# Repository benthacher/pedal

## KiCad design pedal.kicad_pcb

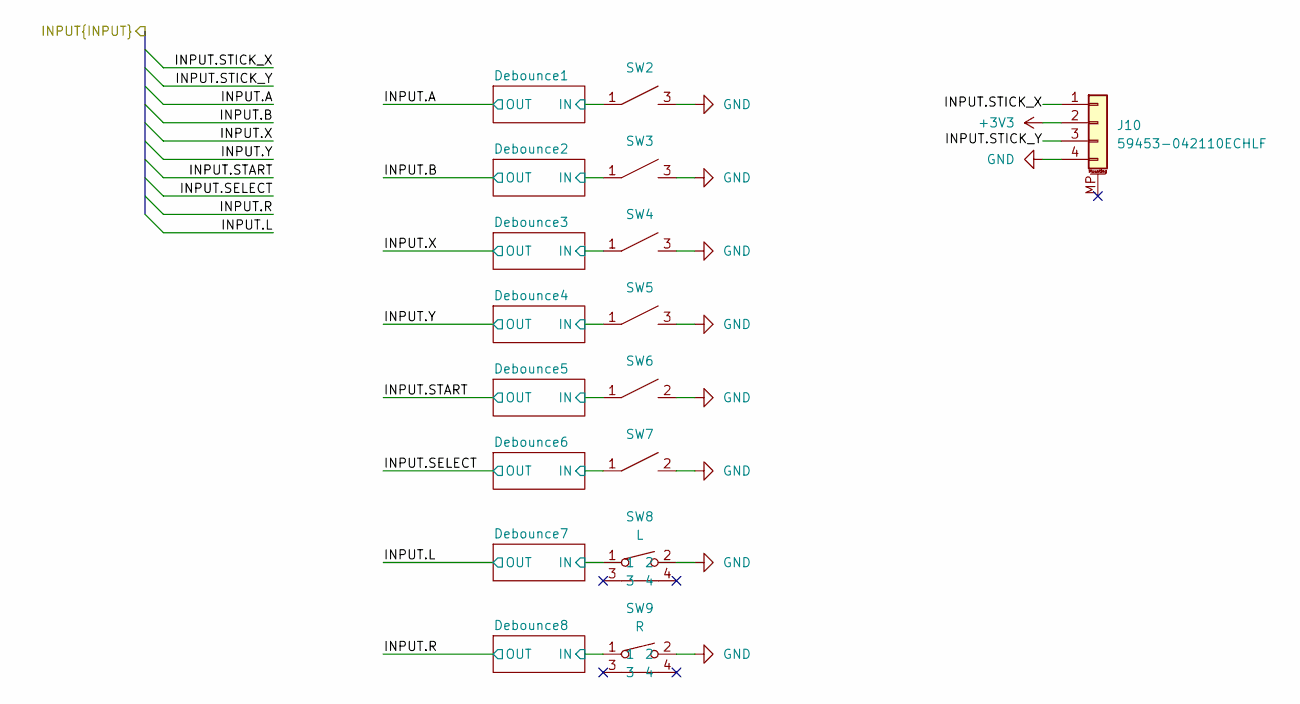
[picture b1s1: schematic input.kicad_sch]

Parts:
J10: 59453-042110ECHLF; AMPHENOL_59453-042110ECHLF; LCSC C3169529
SW2: A; SW-SMD_4P-L4.5-W4.5-P3.50-LS4.8; MPN TL3315NF100Q; LCSC Part C173769
SW3: B; SW-SMD_4P-L4.5-W4.5-P3.50-LS4.8; MPN TL3315NF100Q; LCSC Part C173769
SW4: X; SW-SMD_4P-L4.5-W4.5-P3.50-LS4.8; MPN TL3315NF100Q; LCSC Part C173769
SW5: Y; SW-SMD_4P-L4.5-W4.5-P3.50-LS4.8; MPN TL3315NF100Q; LCSC Part C173769
SW6: START; SW-SMD_L3.9-W3.0-P4.45; MPN TS-1088-AR02016; LCSC Part C720477
SW7: SELECT; SW-SMD_L3.9-W3.0-P4.45; MPN TS-1088-AR02016; LCSC Part C720477
SW8: L; SW-SMD_L4.7-W3.5-P3.35-EH; MPN TS-24CA-S26; LCSC Part C42420265
SW9: R; SW-SMD_L4.7-W3.5-P3.35-EH; MPN TS-24CA-S26; LCSC Part C42420265

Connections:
+3V3: J10.2; also elsewhere on the board
/Input/Debounce1/IN: SW2.1, SW2.2; also elsewhere on the board
/Input/Debounce2/IN: SW3.1, SW3.2; also elsewhere on the board
/Input/Debounce3/IN: SW4.1, SW4.2; also elsewhere on the board
/Input/Debounce4/IN: SW5.1, SW5.2; also elsewhere on the board
/Input/Debounce5/IN: SW6.1; also elsewhere on the board
/Input/Debounce6/IN: SW7.1; also elsewhere on the board
/Input/Debounce7/IN: SW8.1; also elsewhere on the board
/Input/Debounce8/IN: SW9.1; also elsewhere on the board
/Input/INPUT.STICK_X: J10.1; also elsewhere on the board
/Input/INPUT.STICK_Y: J10.3; also elsewhere on the board
GND: J10.4, SW2.3, SW2.4, SW3.3, SW3.4, SW4.3, SW4.4, SW5.3, SW5.4, SW6.2, SW7.2, SW8.2, SW9.2; also elsewhere on the board

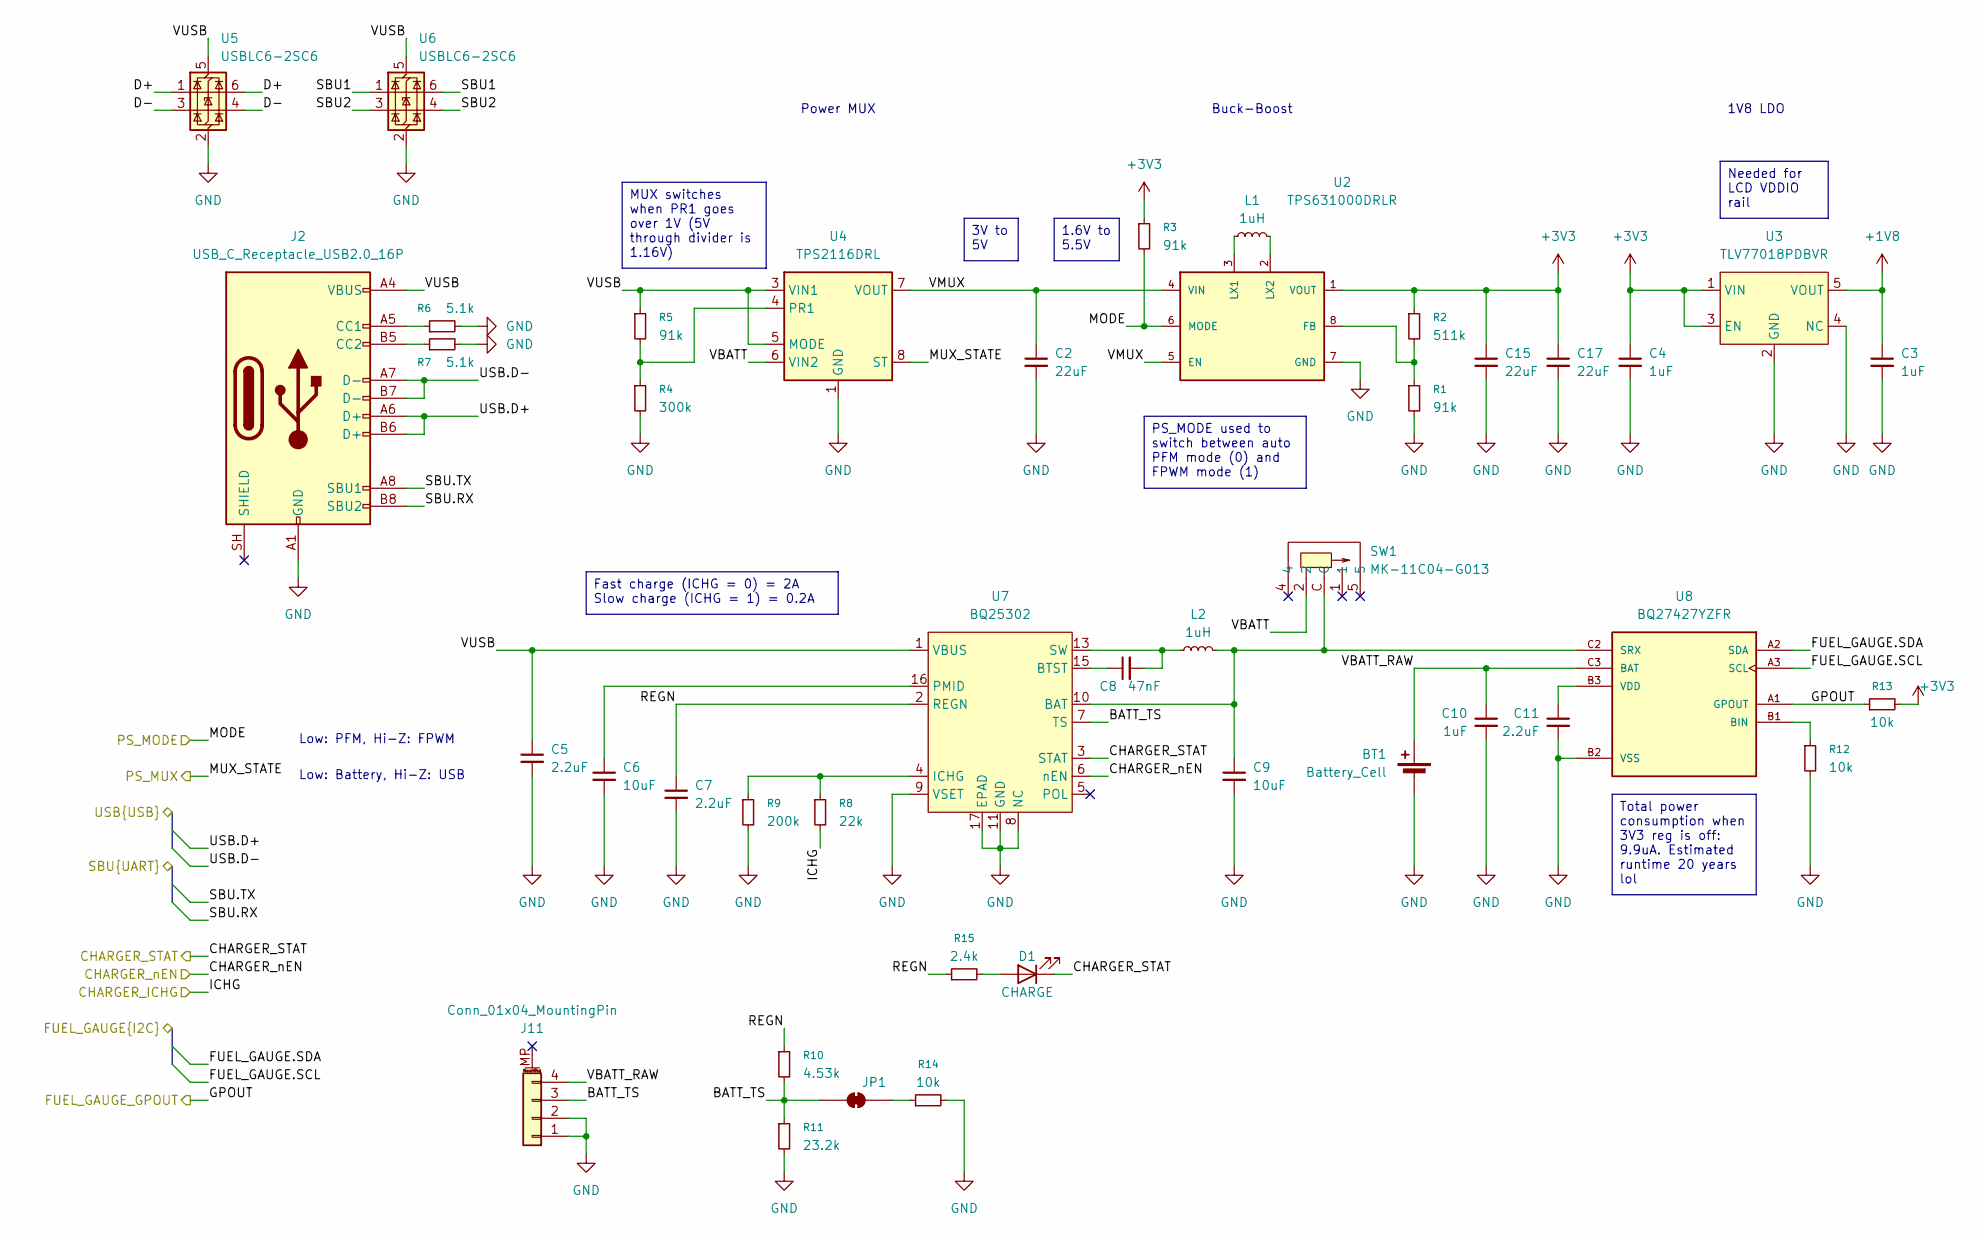
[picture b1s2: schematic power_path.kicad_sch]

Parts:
BT1: Battery_Cell
C2, C15, C17: 22uF; C_0805_2012Metric; Voltage 25V; LCSC C45783
C3: 1uF; C_0402_1005Metric; LCSC C52923
C4, C10: 1uF; C_0402_1005Metric; voltage 25; LCSC C52923
C5, C7, C11: 2.2uF; C_0603_1608Metric; Voltage 16; LCSC C23630
C6, C9: 10uF; C_0603_1608Metric; Voltage 25; LCSC C96446
C8: 47nF; C_0603_1608Metric; Voltage 50; LCSC C1622
D1: CHARGE; LED_0402_1005Metric; LCSC C5123495
J2: USB_C_Receptacle_USB2.0_16P; USB_C_Receptacle_HRO_TYPE-C-31-M-12; LCSC C165948
J11: Conn_01x04_MountingPin; CONN-SMD_4P-P1.00_2121340004
JP1: SolderJumper-2_P1.3mm_Bridged2Bar_RoundedPad1.0x1.5mm
L1, L2: 1uH; L_1008_2520Metric; LCSC C882955
R1, R3, R5: 91k; R_0402_1005Metric; LCSC C327323
R2: 511k; R_0402_1005Metric; LCSC C64042
R4: 300k; R_0402_1005Metric; LCSC C25774
R6, R7: 5.1k; R_0402_1005Metric; LCSC C25905
R8: 22k; R_0402_1005Metric; LCSC C25768
R9: 200k; R_0402_1005Metric; LCSC C25764
R10: 4.53k; R_0402_1005Metric; LCSC C79537
R11: 23.2k; R_0402_1005Metric; LCSC C25873
R12, R13, R14: 10k; R_0402_1005Metric; LCSC C25744
R15: 2.4k; R_0402_1005Metric; LCSC C25882
SW1: MK-11C04-G013; SW-SMD_MK-11C04-G013; MPN MK-11C04-G013; LCSC Part C778185
U2: TPS631000DRLR; SOT50P160X60-8N; PARTREV B; DigiKey_Part_Number 296-TPS631000DRLRCT-ND
U3: TLV77018PDBVR; SOT-23-5
U4: TPS2116DRL; SOT-583-8
U5, U6: USBLC6-2SC6; SOT-23-6; LCSC C5180249
U7: BQ25302; WQFN-16-1EP_3x3mm_P0.5mm_EP1.68x1.68mm_ThermalVias; LCSC C2761617
U8: BQ27427YZFR; IC_BQ27427YZFR; PARTREV December 2022; DigiKey_Part_Number 296-BQ27427YZFRCT-ND

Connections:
+1V8: C3.1, U3.5 (VOUT); also elsewhere on the board
+3V3: C4.1, C15.1, C17.1, R2.1, R3.1, R13.2, U2.1 (VOUT), U3.1 (VIN), U3.3 (EN); also elsewhere on the board
/Power path/BATT_TS: J11.3, JP1.1 (A), R10.2, R11.1, U7.7 (TS)
/Power path/CHARGER_STAT: D1.1 (K), U7.3 (STAT); also elsewhere on the board
/Power path/CHARGER_nEN: U7.6 (nEN); also elsewhere on the board
/Power path/D+: U5.1 (I/O1), U5.6 (I/O1)
/Power path/D-: U5.3 (I/O2), U5.4 (I/O2)
/Power path/FUEL_GAUGE.SCL: U8.A3 (SCL); also elsewhere on the board
/Power path/FUEL_GAUGE.SDA: U8.A2 (SDA); also elsewhere on the board
/Power path/GPOUT: R13.1, U8.A1 (GPOUT); also elsewhere on the board
/Power path/ICHG: R8.2; also elsewhere on the board
/Power path/MODE: R3.2, U2.6 (MODE); also elsewhere on the board
/Power path/MUX_STATE: U4.8 (ST); also elsewhere on the board
/Power path/REGN: C7.1, R10.1, R15.1, U7.2 (REGN)
/Power path/SBU1: U6.1 (I/O1), U6.6 (I/O1)
/Power path/SBU2: U6.3 (I/O2), U6.4 (I/O2)
/Power path/SBU.RX: J2.B8 (SBU2); also elsewhere on the board
/Power path/SBU.TX: J2.A8 (SBU1); also elsewhere on the board
/Power path/USB.D+: J2.A6 (D+), J2.B6 (D+); also elsewhere on the board
/Power path/USB.D-: J2.A7 (D-), J2.B7 (D-); also elsewhere on the board
/Power path/VBATT: SW1.2, U4.6 (VIN2)
/Power path/VBATT_RAW: BT1.1 (+), C10.1, J11.4, U8.C3 (BAT)
/Power path/VMUX: C2.1, U2.4 (VIN), U2.5 (EN), U4.2 (VOUT), U4.7 (VOUT)
/Power path/VUSB: C5.1, J2.A4 (VBUS), J2.A9 (VBUS), J2.B4 (VBUS), J2.B9 (VBUS), R5.1, U4.3 (VIN1), U4.5 (MODE), U5.5 (VBUS), U6.5 (VBUS), U7.1 (VBUS)
GND: BT1.2 (-), C2.2, C3.2, C4.2, C5.2, C6.2, C7.2, C9.2, C10.2, C11.2, C15.2, C17.2, J2.A1 (GND), J2.A12 (GND), J2.B1 (GND), J2.B12 (GND), J11.1, J11.2, R1.2, R4.2, R6.2, R7.2, R9.2, R11.2, R12.2, R14.2, U2.7 (GND), U3.2 (GND), U3.4 (NC), U4.1 (GND), U5.2 (GND), U6.2 (GND), U7.8 (NC), U7.9 (VSET), U7.11 (GND), U7.12 (GND), U7.17 (EPAD), U8.B2 (VSS), U8.C1 (VSS); also elsewhere on the board
unnamed: C8.2, L2.1, U7.13 (SW), U7.14 (SW)
unnamed: D1.2 (A), R15.2
unnamed: J2.A5 (CC1), R6.1
unnamed: J2.B5 (CC2), R7.1
unnamed: JP1.2 (B), R14.1
unnamed: R1.1, R2.2, U2.8 (FB)
unnamed: L1.1, U2.3 (LX1)
unnamed: L1.2, U2.2 (LX2)
unnamed: R4.1, R5.2, U4.4 (PR1)
unnamed: C9.1, L2.2, SW1.C, U7.10 (BAT), U8.C2 (SRX)
unnamed: C8.1, U7.15 (BTST)
unnamed: R8.1, R9.1, U7.4 (ICHG)
unnamed: C6.1, U7.16 (PMID)
unnamed: R12.1, U8.B1 (BIN)
unnamed: C11.1, U8.B3 (VDD)

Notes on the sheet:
Low: Battery, Hi-Z: USB
1V8 LDO
Buck-Boost
Low: PFM, Hi-Z: FPWM
Power MUX
Total power consumption when 3V3 reg is off: 9.9uA. Estimated runtime 20 years lol
3V to 5V
Needed for LCD VDDIO rail
MUX switches when PR1 goes over 1V (5V through divider is 1.16V)
1.6V to 5.5V
Fast charge (ICHG = 0) = 2A Slow charge (ICHG = 1) = 0.2A
PS_MODE used to switch between auto PFM mode (0) and FPWM mode (1)

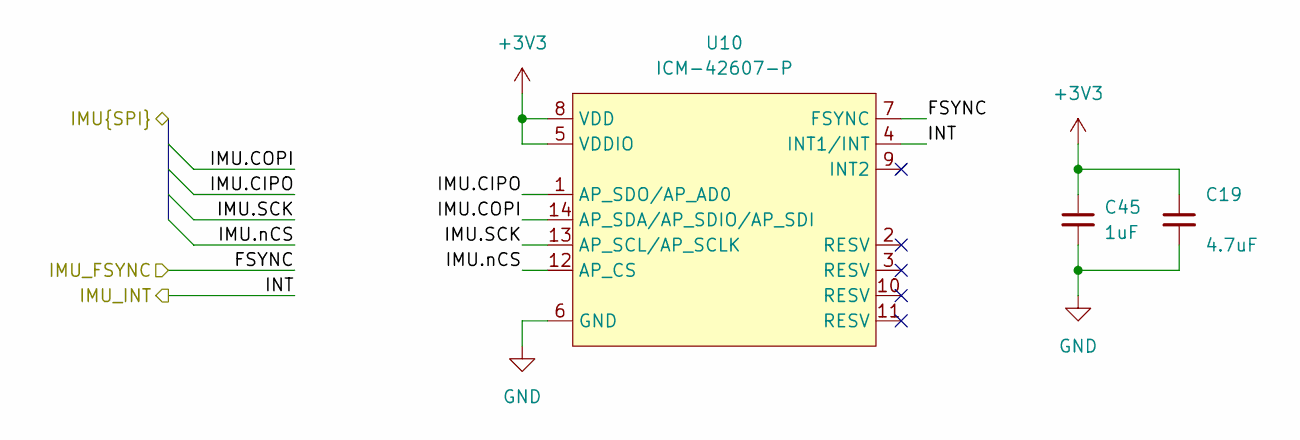
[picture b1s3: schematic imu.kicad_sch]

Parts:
C19: 4.7uF; C_0402_1005Metric; LCSC C23733
C45: 1uF; C_0402_1005Metric; voltage 25; LCSC C52923
U10: ICM-42607-P; LGA-14_L3.0-W2.5-P0.50-TL_QMI8658A; MPN ICM-42607-P; LCSC Part C5129967

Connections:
+3V3: C19.1, C45.1, U10.5 (VDDIO), U10.8 (VDD); also elsewhere on the board
/IMU/FSYNC: U10.7 (FSYNC); also elsewhere on the board
/IMU/IMU.CIPO: U10.1 (AP_SDO/AP_AD0); also elsewhere on the board
/IMU/IMU.COPI: U10.14 (AP_SDA/AP_SDIO/AP_SDI); also elsewhere on the board
/IMU/IMU.SCK: U10.13 (AP_SCL/AP_SCLK); also elsewhere on the board
/IMU/IMU.nCS: U10.12 (AP_CS); also elsewhere on the board
/IMU/INT: U10.4 (INT1/INT); also elsewhere on the board
GND: C19.2, C45.2, U10.6 (GND); also elsewhere on the board

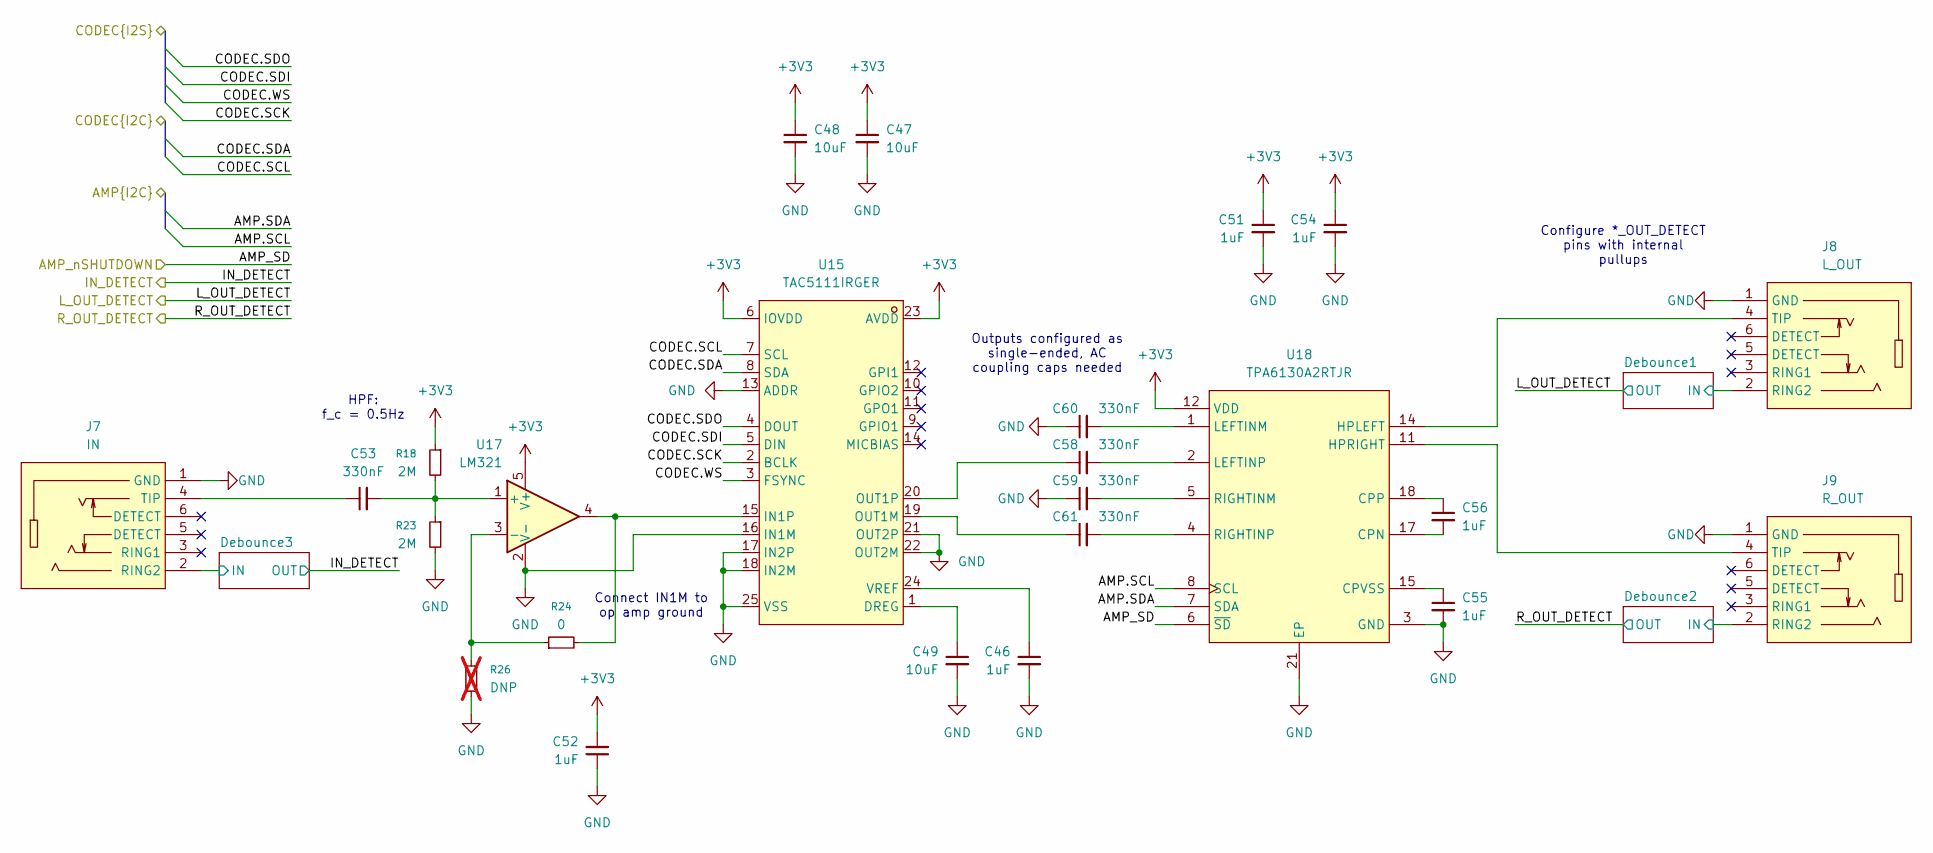
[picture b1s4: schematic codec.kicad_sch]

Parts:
C46, C51, C52, C54, C55, C56: 1uF; C_0402_1005Metric; voltage 25; LCSC C52923
C47, C48, C49: 10uF; C_0603_1608Metric; Voltage 25; LCSC C96446
C53, C58, C59, C60, C61: 330nF; C_1206_3216Metric; Voltage 25; LCSC C3837965
J7: IN; AUDIO-SMD_PJ-342-141; MPN PJ-342 141; LCSC Part C7507452
J8: L_OUT; AUDIO-SMD_PJ-342-141; MPN PJ-342 141; LCSC Part C7507452
J9: R_OUT; AUDIO-SMD_PJ-342-141; MPN PJ-342 141; LCSC Part C7507452
R18, R23: 2M; R_0603_1608Metric; LCSC C22976
R24: 0; R_0402_1005Metric; LCSC C17168
R26: DNP; R_0402_1005Metric; not fitted
U15: TAC5111IRGER; VQFN-24_L4.0-W4.0-P0.50-BL-EP2.1_1; MPN TAC5111IRGER; LCSC Part C45335502
U17: LM321; SC-70-5_L2.1-W1.3-P0.65-LS2.1-BR
U18: TPA6130A2RTJR; QFN-20_L4.0-W4.0-P0.5-TL-EP; MPN TPA6130A2RTJR; LCSC Part C130046

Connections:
+3V3: C47.1, C48.1, C51.1, C52.2, C54.1, R18.1, U15.6 (IOVDD), U15.23 (AVDD), U17.5 (V+), U18.12 (VDD), U18.20 (VDD); also elsewhere on the board
/Codec/AMP.SCL: U18.8 (SCL); also elsewhere on the board
/Codec/AMP.SDA: U18.7 (SDA); also elsewhere on the board
/Codec/AMP_SD: U18.6 (~SD); also elsewhere on the board
/Codec/CODEC.SCK: U15.2 (BCLK); also elsewhere on the board
/Codec/CODEC.SCL: U15.7 (SCL); also elsewhere on the board
/Codec/CODEC.SDA: U15.8 (SDA); also elsewhere on the board
/Codec/CODEC.SDI: U15.5 (DIN); also elsewhere on the board
/Codec/CODEC.SDO: U15.4 (DOUT); also elsewhere on the board
/Codec/CODEC.WS: U15.3 (FSYNC); also elsewhere on the board
/Codec/Debounce1/IN: J8.2 (RING2); also elsewhere on the board
/Codec/Debounce2/IN: J9.2 (RING2); also elsewhere on the board
/Codec/Debounce3/IN: J7.2 (RING2); also elsewhere on the board
CPVSS: C55.1, U18.15 (CPVSS), U18.16 (CPVSS)
GND: C46.2, C47.2, C48.2, C49.2, C51.2, C52.1, C54.2, C55.2, C59.1, C60.1, J7.1 (GND), J8.1 (GND), J9.1 (GND), R23.2, R26.1, U15.13 (ADDR), U15.16 (IN1M), U15.17 (IN2P), U15.18 (IN2M), U15.21 (OUT2P), U15.22 (OUT2M), U15.25 (VSS), U15.A1 (VSS), U15.A2 (VSS), U15.A3 (VSS), U15.A4 (VSS), U17.2 (V-), U18.3 (GND), U18.9 (GND), U18.10 (GND), U18.13 (GND), U18.19 (GND), U18.21 (EP); also elsewhere on the board
unnamed: C53.1, J7.4 (TIP)
unnamed: J8.4 (TIP), U18.14 (HPLEFT)
unnamed: J9.4 (TIP), U18.11 (HPRIGHT)
unnamed: C49.1, U15.1 (DREG)
unnamed: R24.2, U15.15 (IN1P), U17.4
unnamed: C61.1, U15.19 (OUT1M)
unnamed: C58.1, U15.20 (OUT1P)
unnamed: C46.1, U15.24 (VREF)
unnamed: C53.2, R18.2, R23.1, U17.1 (+)
unnamed: R24.1, R26.2, U17.3 (-)
unnamed: C56.2, U18.17 (CPN)
unnamed: C56.1, U18.18 (CPP)
unnamed: C60.2, U18.1 (LEFTINM)
unnamed: C58.2, U18.2 (LEFTINP)
unnamed: C59.2, U18.5 (RIGHTINM)
unnamed: C61.2, U18.4 (RIGHTINP)

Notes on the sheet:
Connect IN1M to op amp ground
Configure *_OUT_DETECT pins with internal pullups
HPF: f_c = 0.5Hz
Outputs configured as single-ended, AC coupling caps needed

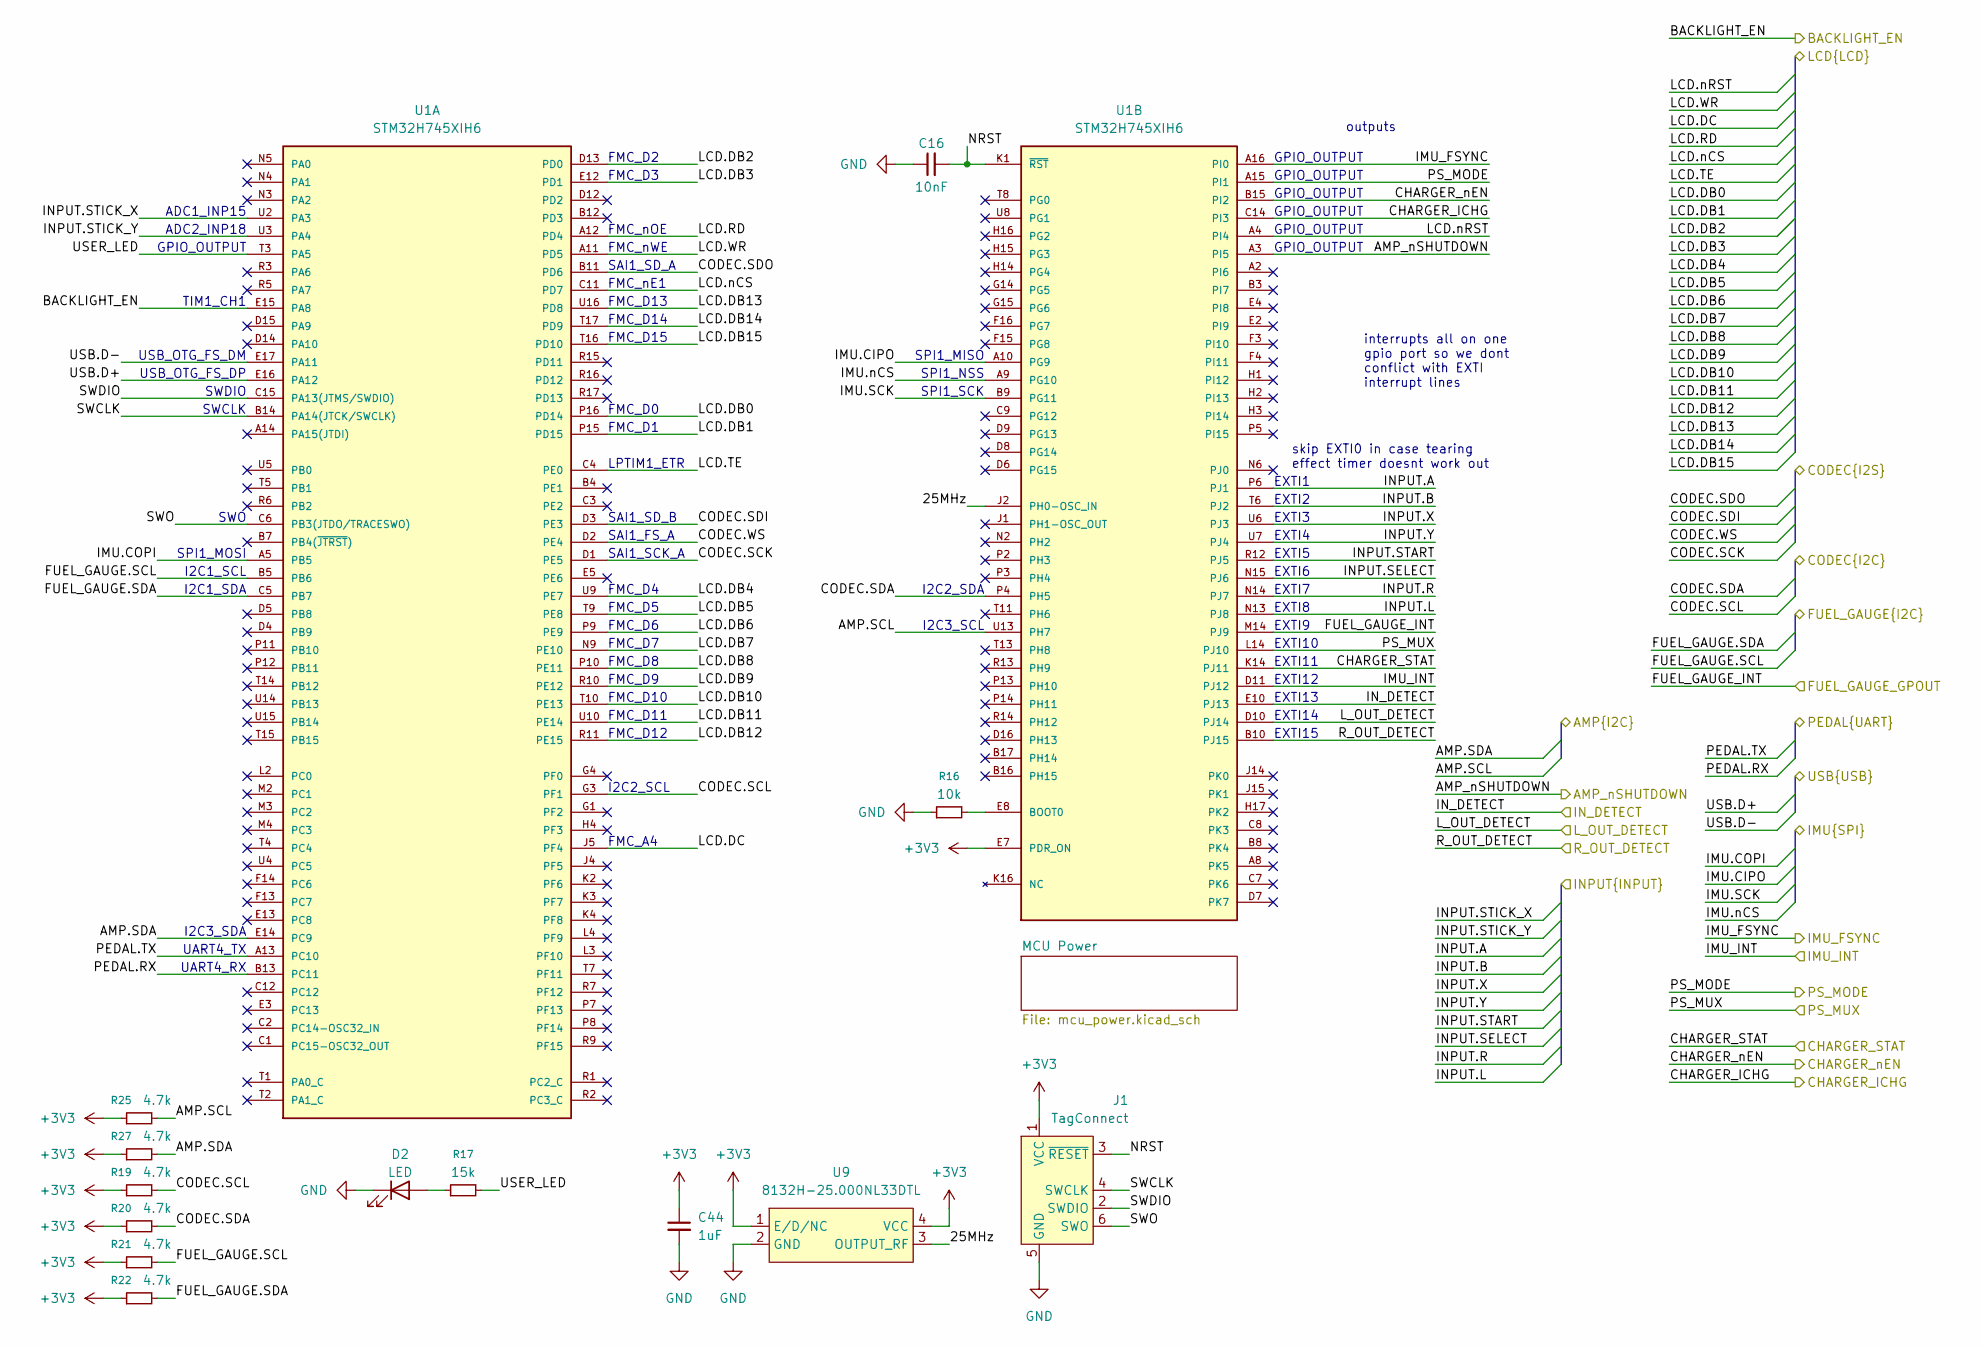
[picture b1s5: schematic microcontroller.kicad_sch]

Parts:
C16: 10nF; C_0402_1005Metric; Voltage 50V; LCSC C15195
C44: 1uF; C_0402_1005Metric; voltage 25; LCSC C52923
D2: LED; LED_0402_1005Metric; LCSC C965793
J1: TagConnect; Tag-Connect_TC2030-IDC-NL_2x03_P1.27mm_Vertical
R16: 10k; R_0402_1005Metric; LCSC C25744
R17: 15k; R_0402_1005Metric; LCSC C25756
R19, R20, R21, R22, R25, R27: 4.7k; R_0402_1005Metric; LCSC C25900
U1: STM32H745XIH6; BGA265C80P17X17_1400X1400X120; PARTREV 3; LCSC C1338373
U9: 8132H-25.000NL33DTL; OSC-SMD_4P-L3.2-W2.5-BL; MPN 8132H-25.000NL33DTL; LCSC Part C46598430

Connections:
+3V3: C44.1, J1.1 (VCC), R19.1, R20.1, R21.1, R22.1, R25.1, R27.1, U1.E7 (PDR_ON), U9.1 (E/D/NC), U9.4 (VCC); also elsewhere on the board
/Codec/AMP.SCL: R25.2, U1.U13 (PH7); also elsewhere on the board
/Codec/AMP.SDA: R27.2, U1.E14 (PC9); also elsewhere on the board
/Codec/AMP_SD: U1.A3 (PI5); also elsewhere on the board
/Codec/CODEC.SCK: U1.D1 (PE5); also elsewhere on the board
/Codec/CODEC.SCL: R19.2, U1.G3 (PF1); also elsewhere on the board
/Codec/CODEC.SDA: R20.2, U1.P4 (PH5); also elsewhere on the board
/Codec/CODEC.SDI: U1.D3 (PE3); also elsewhere on the board
/Codec/CODEC.SDO: U1.B11 (PD6); also elsewhere on the board
/Codec/CODEC.WS: U1.D2 (PE4); also elsewhere on the board
/Codec/IN_DETECT: U1.E10 (PJ13); also elsewhere on the board
/Codec/L_OUT_DETECT: U1.D10 (PJ14); also elsewhere on the board
/Codec/R_OUT_DETECT: U1.B10 (PJ15); also elsewhere on the board
/IMU/FSYNC: U1.A16 (PI0); also elsewhere on the board
/IMU/IMU.CIPO: U1.A10 (PG9); also elsewhere on the board
/IMU/IMU.COPI: U1.A5 (PB5); also elsewhere on the board
/IMU/IMU.SCK: U1.B9 (PG11); also elsewhere on the board
/IMU/IMU.nCS: U1.A9 (PG10); also elsewhere on the board
/IMU/INT: U1.D11 (PJ12); also elsewhere on the board
/Input/INPUT.A: U1.P6 (PJ1); also elsewhere on the board
/Input/INPUT.B: U1.T6 (PJ2); also elsewhere on the board
/Input/INPUT.L: U1.N13 (PJ8); also elsewhere on the board
/Input/INPUT.R: U1.N14 (PJ7); also elsewhere on the board
/Input/INPUT.SELECT: U1.N15 (PJ6); also elsewhere on the board
/Input/INPUT.START: U1.R12 (PJ5); also elsewhere on the board
/Input/INPUT.STICK_X: U1.U2 (PA3); also elsewhere on the board
/Input/INPUT.STICK_Y: U1.U3 (PA4); also elsewhere on the board
/Input/INPUT.X: U1.U6 (PJ3); also elsewhere on the board
/Input/INPUT.Y: U1.U7 (PJ4); also elsewhere on the board
/Power path/CHARGER_STAT: U1.K14 (PJ11); also elsewhere on the board
/Power path/CHARGER_nEN: U1.B15 (PI2); also elsewhere on the board
/Power path/FUEL_GAUGE.SCL: R21.2, U1.B5 (PB6); also elsewhere on the board
/Power path/FUEL_GAUGE.SDA: R22.2, U1.C5 (PB7); also elsewhere on the board
/Power path/GPOUT: U1.M14 (PJ9); also elsewhere on the board
/Power path/ICHG: U1.C14 (PI3); also elsewhere on the board
/Power path/MODE: U1.A15 (PI1); also elsewhere on the board
/Power path/MUX_STATE: U1.L14 (PJ10); also elsewhere on the board
/Power path/SBU.RX: U1.B13 (PC11); also elsewhere on the board
/Power path/SBU.TX: U1.A13 (PC10); also elsewhere on the board
/Power path/USB.D+: U1.E16 (PA12); also elsewhere on the board
/Power path/USB.D-: U1.E17 (PA11); also elsewhere on the board
/display/LCD.DB0: U1.P16 (PD14); also elsewhere on the board
/display/LCD.DB1: U1.P15 (PD15); also elsewhere on the board
/display/LCD.DB2: U1.D13 (PD0); also elsewhere on the board
/display/LCD.DB3: U1.E12 (PD1); also elsewhere on the board
/display/LCD.DB4: U1.U9 (PE7); also elsewhere on the board
/display/LCD.DB5: U1.T9 (PE8); also elsewhere on the board
/display/LCD.DB6: U1.P9 (PE9); also elsewhere on the board
/display/LCD.DB7: U1.N9 (PE10); also elsewhere on the board
/display/LCD.DB8: U1.P10 (PE11); also elsewhere on the board
/display/LCD.DB9: U1.R10 (PE12); also elsewhere on the board
/display/LCD.DB10: U1.T10 (PE13); also elsewhere on the board
/display/LCD.DB11: U1.U10 (PE14); also elsewhere on the board
/display/LCD.DB12: U1.R11 (PE15); also elsewhere on the board
/display/LCD.DB13: U1.U16 (PD8); also elsewhere on the board
/display/LCD.DB14: U1.T17 (PD9); also elsewhere on the board
/display/LCD.DB15: U1.T16 (PD10); also elsewhere on the board
/display/LCD.DC: U1.J5 (PF4); also elsewhere on the board
/display/LCD.RD: U1.A12 (PD4); also elsewhere on the board
/display/LCD.TE: U1.C4 (PE0); also elsewhere on the board
/display/LCD.WR: U1.A11 (PD5); also elsewhere on the board
/display/LCD.nCS: U1.C11 (PD7); also elsewhere on the board
/display/LCD.nRST: U1.A4 (PI4); also elsewhere on the board
/microcontroller/25MHz: U1.J2 (PH0-OSC_IN), U9.3 (OUTPUT_RF)
/microcontroller/BACKLIGHT_EN: U1.E15 (PA8); also elsewhere on the board
/microcontroller/NRST: C16.2, J1.3 (~RESET), U1.K1 (~RST)
/microcontroller/SWCLK: J1.4 (SWCLK), U1.B14 (PA14(JTCK/SWCLK))
/microcontroller/SWDIO: J1.2 (SWDIO), U1.C15 (PA13(JTMS/SWDIO))
/microcontroller/SWO: J1.6 (SWO), U1.C6 (PB3(JTDO/TRACESWO))
/microcontroller/USER_LED: R17.2, U1.T3 (PA5)
GND: C16.1, C44.2, D2.1 (K), J1.5 (GND), R16.1, U9.2 (GND); also elsewhere on the board
unnamed: D2.2 (A), R17.1
unnamed: R16.2, U1.E8 (BOOT0)

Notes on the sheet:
SAI1_SD_B
LPTIM1_ETR
SPI1_SCK
outputs
EXTI5
FMC_D7
EXTI9
EXTI7
ADC2_INP18
SPI1_MOSI
FMC_D6
I2C1_SCL
FMC_D9
I2C2_SCL
I2C2_SDA
FMC_nE1
FMC_D0
EXTI3
EXTI4
FMC_D5
EXTI6
SAI1_SD_A
FMC_nOE
I2C1_SDA
FMC_D10
FMC_nWE
GPIO_OUTPUT
EXTI13
EXTI10
EXTI15
ADC1_INP15
FMC_D12
SWO
FMC_D13
SWDIO
FMC_A4
FMC_D4
SAI1_SCK_A
FMC_D14
EXTI11

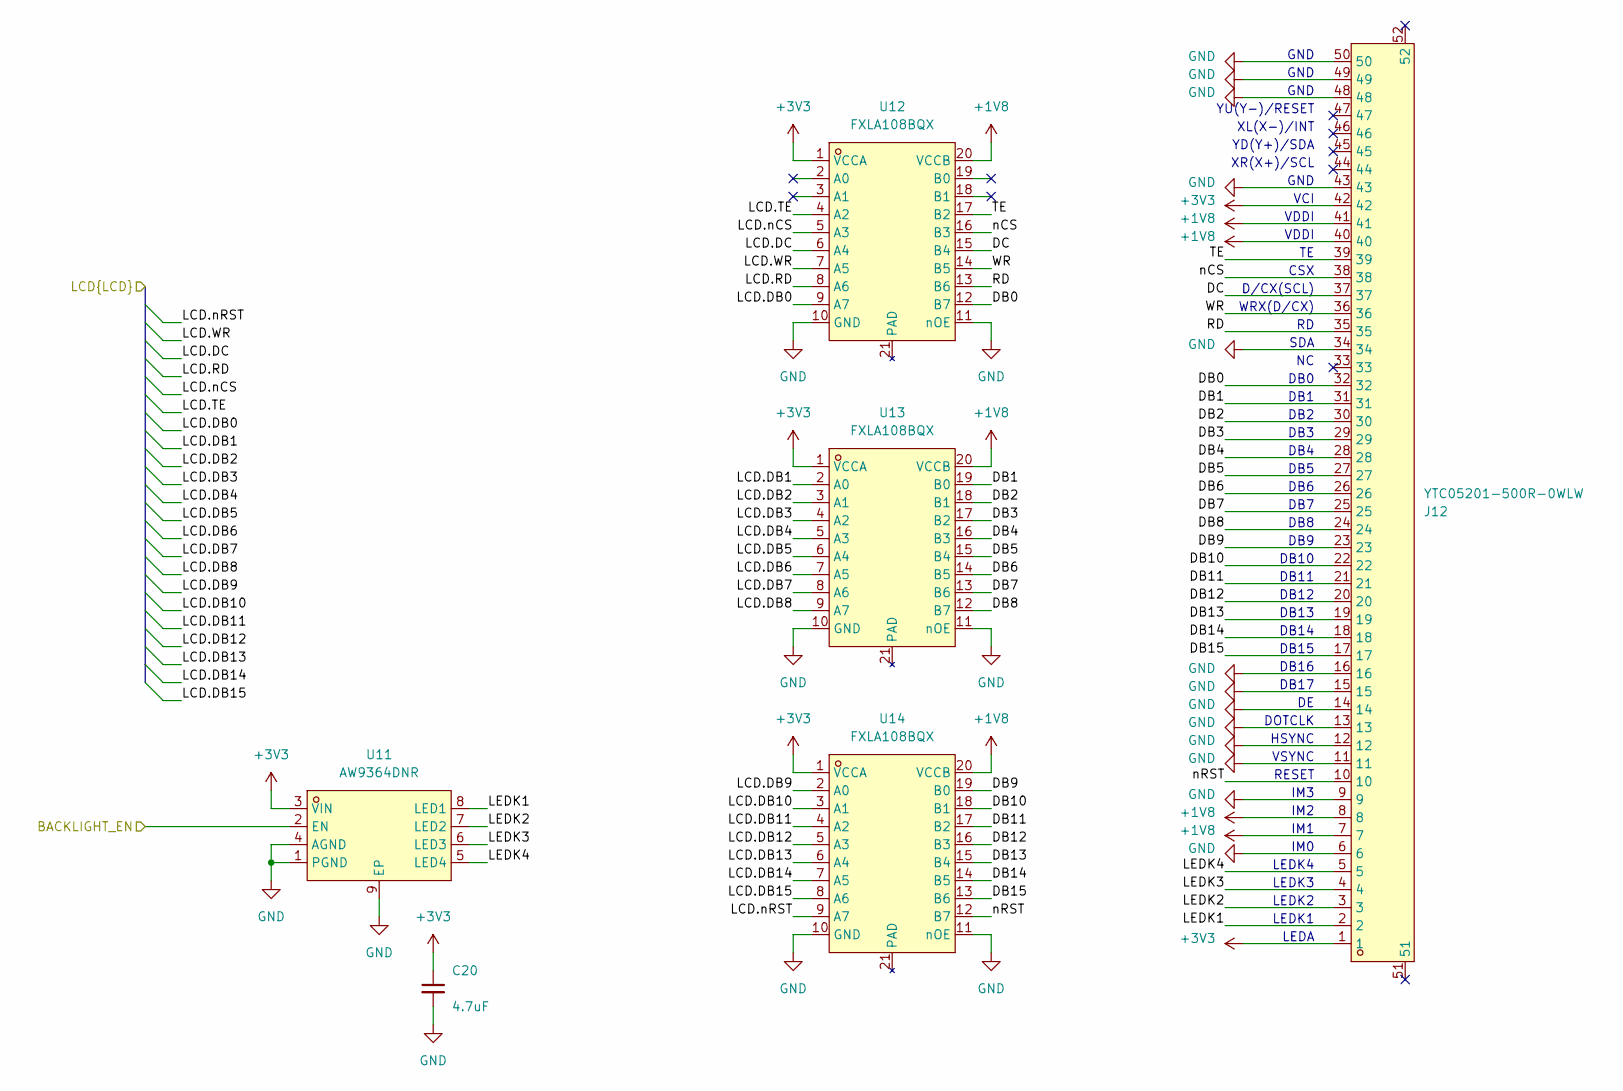
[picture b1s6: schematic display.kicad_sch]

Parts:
C20: 4.7uF; C_0402_1005Metric; LCSC C23733
J12: YTC05201-500R-0WLW; FPC-SMD_50P-P0.50_YTC05201-500R-0WLW; MPN YTC05201-500R-0WLW; LCSC Part C19673900
U11: AW9364DNR; DFN-8_L2.0-W2.0-P0.50-BL-EP-1; MPN AW9364DNR; LCSC Part C401007
U12, U13, U14: FXLA108BQX; DHVQFN-20_L4.5-W2.5-P0.50-BL-EP; MPN FXLA108BQX; LCSC Part C603076

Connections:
+1V8: J12.7, J12.8, J12.40, J12.41, U12.20 (VCCB), U13.20 (VCCB), U14.20 (VCCB); also elsewhere on the board
+3V3: C20.1, J12.1, J12.42, U11.3 (VIN), U12.1 (VCCA), U13.1 (VCCA), U14.1 (VCCA); also elsewhere on the board
/display/DB0: J12.32, U12.12 (B7)
/display/DB1: J12.31, U13.19 (B0)
/display/DB2: J12.30, U13.18 (B1)
/display/DB3: J12.29, U13.17 (B2)
/display/DB4: J12.28, U13.16 (B3)
/display/DB5: J12.27, U13.15 (B4)
/display/DB6: J12.26, U13.14 (B5)
/display/DB7: J12.25, U13.13 (B6)
/display/DB8: J12.24, U13.12 (B7)
/display/DB9: J12.23, U14.19 (B0)
/display/DB10: J12.22, U14.18 (B1)
/display/DB11: J12.21, U14.17 (B2)
/display/DB12: J12.20, U14.16 (B3)
/display/DB13: J12.19, U14.15 (B4)
/display/DB14: J12.18, U14.14 (B5)
/display/DB15: J12.17, U14.13 (B6)
/display/DC: J12.37, U12.15 (B4)
/display/LCD.DB0: U12.9 (A7); also elsewhere on the board
/display/LCD.DB1: U13.2 (A0); also elsewhere on the board
/display/LCD.DB2: U13.3 (A1); also elsewhere on the board
/display/LCD.DB3: U13.4 (A2); also elsewhere on the board
/display/LCD.DB4: U13.5 (A3); also elsewhere on the board
/display/LCD.DB5: U13.6 (A4); also elsewhere on the board
/display/LCD.DB6: U13.7 (A5); also elsewhere on the board
/display/LCD.DB7: U13.8 (A6); also elsewhere on the board
/display/LCD.DB8: U13.9 (A7); also elsewhere on the board
/display/LCD.DB9: U14.2 (A0); also elsewhere on the board
/display/LCD.DB10: U14.3 (A1); also elsewhere on the board
/display/LCD.DB11: U14.4 (A2); also elsewhere on the board
/display/LCD.DB12: U14.5 (A3); also elsewhere on the board
/display/LCD.DB13: U14.6 (A4); also elsewhere on the board
/display/LCD.DB14: U14.7 (A5); also elsewhere on the board
/display/LCD.DB15: U14.8 (A6); also elsewhere on the board
/display/LCD.DC: U12.6 (A4); also elsewhere on the board
/display/LCD.RD: U12.8 (A6); also elsewhere on the board
/display/LCD.TE: U12.4 (A2); also elsewhere on the board
/display/LCD.WR: U12.7 (A5); also elsewhere on the board
/display/LCD.nCS: U12.5 (A3); also elsewhere on the board
/display/LCD.nRST: U14.9 (A7); also elsewhere on the board
/display/LEDK1: J12.2, U11.8 (LED1)
/display/LEDK2: J12.3, U11.7 (LED2)
/display/LEDK3: J12.4, U11.6 (LED3)
/display/LEDK4: J12.5, U11.5 (LED4)
/display/RD: J12.35, U12.13 (B6)
/display/TE: J12.39, U12.17 (B2)
/display/WR: J12.36, U12.14 (B5)
/display/nCS: J12.38, U12.16 (B3)
/display/nRST: J12.10, U14.12 (B7)
/microcontroller/BACKLIGHT_EN: U11.2 (EN); also elsewhere on the board
GND: C20.2, J12.6, J12.9, J12.11, J12.12, J12.13, J12.14, J12.15, J12.16, J12.34, J12.43, J12.48, J12.49, J12.50, U11.1 (PGND), U11.4 (AGND), U11.9 (EP), U12.10 (GND), U12.11 (nOE), U13.10 (GND), U13.11 (nOE), U14.10 (GND), U14.11 (nOE); also elsewhere on the board

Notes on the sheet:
VDDI
DB10
RESET
DB0
DB13
LEDK4
IM2
DB4
GND
DB5
LEDK3
IM1
VCI
XL(X-)/INT
DB7
D/CX(SCL)
DB17
LEDK1
IM0
SDA
DB14
DB11
DB3
LEDK2
DB9
YD(Y+)/SDA
DB12
DB15
CSX
XR(X+)/SCL
HSYNC
LEDA
DB8
YU(Y-)/RESET
WRX(D/CX)
VSYNC
IM3
DB16
DB2
DB1

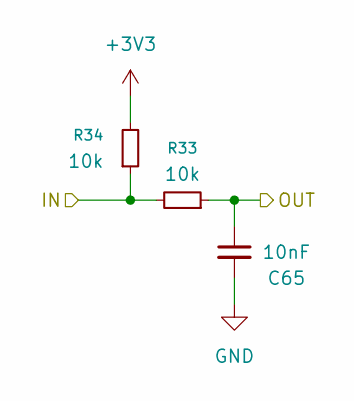
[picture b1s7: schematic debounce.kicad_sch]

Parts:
C65: 10nF; C_0402_1005Metric; Voltage 50V; LCSC C15195
R33, R34: 10k; R_0402_1005Metric; LCSC C25744

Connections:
+3V3: R34.2; also elsewhere on the board
/Codec/Debounce1/IN: R33.2, R34.1; also elsewhere on the board
/Codec/L_OUT_DETECT: C65.1, R33.1; also elsewhere on the board
GND: C65.2; also elsewhere on the board

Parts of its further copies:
C66, C67, C68, C69, C70, C71, C72, C73, C74, C75: 10nF; C_0402_1005Metric; Voltage 50V; LCSC C15195
R35, R36, R37, R38, R39, R40, R41, R42, R43, R44, R45, R46, R47, R48, R49, R50, R51, R52, R53, R54: 10k; R_0402_1005Metric; LCSC C25744

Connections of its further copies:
+3V3: R35.2, R37.2, R39.2, R41.2, R43.2, R45.2, R47.2, R49.2, R51.2, R53.2; also elsewhere on the board
/Codec/Debounce2/IN: R35.1, R36.2; also elsewhere on the board
/Codec/Debounce3/IN: R37.1, R38.2; also elsewhere on the board
/Codec/IN_DETECT: C67.1, R38.1; also elsewhere on the board
/Codec/R_OUT_DETECT: C66.1, R36.1; also elsewhere on the board
/Input/Debounce1/IN: R39.1, R40.2; also elsewhere on the board
/Input/Debounce2/IN: R41.1, R42.2; also elsewhere on the board
/Input/Debounce3/IN: R43.1, R44.2; also elsewhere on the board
/Input/Debounce4/IN: R45.1, R46.2; also elsewhere on the board
/Input/Debounce5/IN: R47.1, R48.2; also elsewhere on the board
/Input/Debounce6/IN: R49.1, R50.2; also elsewhere on the board
/Input/Debounce7/IN: R51.1, R52.2; also elsewhere on the board
/Input/Debounce8/IN: R53.1, R54.2; also elsewhere on the board
/Input/INPUT.A: C68.1, R40.1; also elsewhere on the board
/Input/INPUT.B: C69.1, R42.1; also elsewhere on the board
/Input/INPUT.L: C74.1, R52.1; also elsewhere on the board
/Input/INPUT.R: C75.1, R54.1; also elsewhere on the board
/Input/INPUT.SELECT: C73.1, R50.1; also elsewhere on the board
/Input/INPUT.START: C72.1, R48.1; also elsewhere on the board
/Input/INPUT.X: C70.1, R44.1; also elsewhere on the board
/Input/INPUT.Y: C71.1, R46.1; also elsewhere on the board
GND: C66.2, C67.2, C68.2, C69.2, C70.2, C71.2, C72.2, C73.2, C74.2, C75.2; also elsewhere on the board
